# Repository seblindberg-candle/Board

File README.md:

# Candle Board

The EAGLE Cad board files for the Candle project can be found here.

## TODO

- [x] Add a pull-up on the flash memory chip select line.
- [x] Fix the MOSFET orientation.
- [x] Fix the flash memory footprint.
- [x] Remove the hole.
- [x] Remove the microphone
- [ ] Switch out the power supply.
- [ ] Move the status LEDs to the back.
- [ ] Move the button to a more reachable position
- [ ] Make the serial port easier to connect to
- [ ] Increase the board length to 25-30 cm
- [x] Bias the display driver current sense line with the DAC
- [ ] Add one or two light sensors (front and/or back)

The following hardware changes are based on features/limitations in the peripherals that where not discovered until after the first revision.

- [ ] Connect the flash memory to `SPIC`
- [ ] Connect the display driver to `USARTD0`
- [ ] Connect `DISP_LE` to an event output (`PC4`, `PC7`, `PD4` or `PD7`)
- [ ] Connect `DISP_OE` to a compare output (`PD2`, since it is unused)
- [ ] Connect the board serial port to `USARTC0`

## Revisions

Board revisions are kept as tags in git. The board is generally tagged when the files have been sent off for manufacturing. To export a specific revision, simply run

```
$ git archive --format zip -o /path/to/rev-a.zip 4d268f
```

where the hash of the tag can be found by running `git show rev-a` for the specific tag.

## Notes

### MOSFET Pull-ups

The pull-ups are required because of the internal protection diods in the main IC. They will not allow the voltage to exceed ~3.8 V. The resistors connected to the gates thus serve to:

1. protect the gate from inrush current,
2. pull the gate high on startup and
3. set the voltage at the gate to a value above the turn-on threshold.

## Scripts

Some ruby scripts are included for generating EAGLE commands that place some of the more repetitive components. There are tools in EAGLE for achieving the same thing and they are most likely better, but a) I did not know that at the time and b) the scripts allowed be to also remove the labels, which would otherwise have been quite a task in itself. 

To run the scripts you need to locate the Scripts folder in your terminal of choice and type `ruby place-diods.rb`. Then press `enter` and copy the output into the command input in EAGLE.

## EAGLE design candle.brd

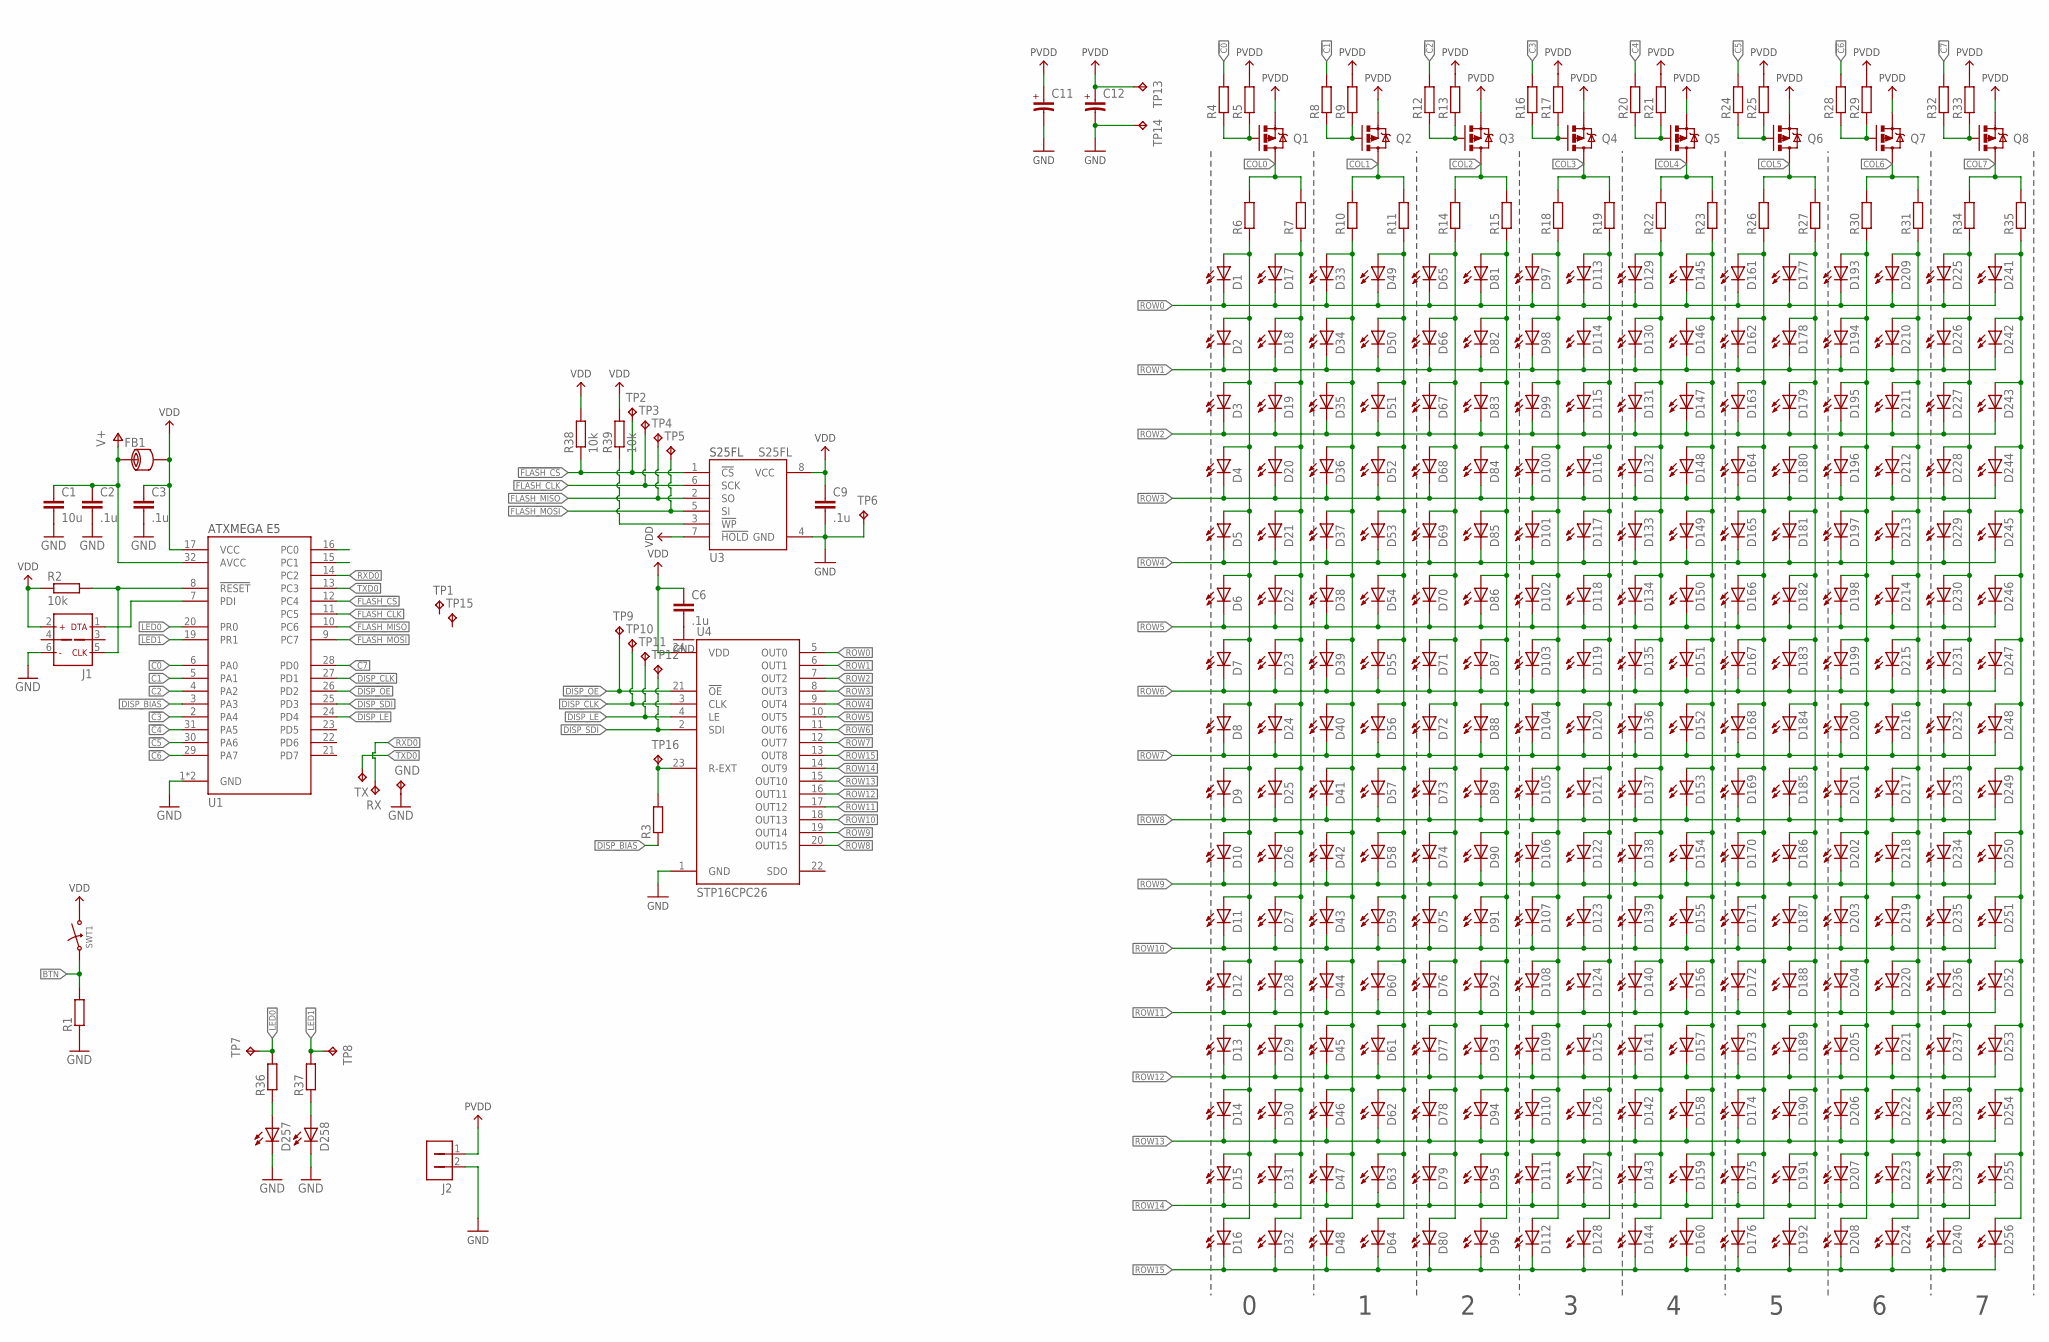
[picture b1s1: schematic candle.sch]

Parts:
C1: 10u; 0805
C2, C3, C6, C9: .1u; 0805
C11, C12: C_POL_1206; 1206_POL
D1, D2, D3, D4, D5, D6, D7, D8, D9, D10, D11, D12, D13, D14, D15, D16, D17, D18, D19, D20, D21, D22, D23, D24, D25, D26, D27, D28, D29, D30, D31, D32, D33, D34, D35, D36, D37, D38, D39, D40, D41, D42, D43, D44, D45, D46, D47, D48, D49, D50, D51, D52, D53, D54, D55, D56, D57, D58, D59, D60, D61, D62, D63, D64, D65, D66, D67, D68, D69, D70, D71, D72, D73, D74, D75, D76, D77, D78, D79, D80, D81, D82, D83, D84, D85, D86, D87, D88, D89, D90, D91, D92, D93, D94, D95, D96, D97, D98, D99, D100, D101, D102, D103, D104, D105, D106, D107, D108, D109, D110, D111, D112, D113, D114, D115, D116, D117, D118, D119, D120, D121, D122, D123, D124, D125, D126, D127, D128, D129, D130, D131, D132, D133, D134, D135, D136, D137, D138, D139, D140, D141, D142, D143, D144, D145, D146, D147, D148, D149, D150, D151, D152, D153, D154, D155, D156, D157, D158, D159, D160, D161, D162, D163, D164, D165, D166, D167, D168, D169, D170, D171, D172, D173, D174, D175, D176, D177, D178, D179, D180, D181, D182, D183, D184, D185, D186, D187, D188, D189, D190, D191, D192, D193, D194, D195, D196, D197, D198, D199, D200, D201, D202, D203, D204, D205, D206, D207, D208, D209, D210, D211, D212, D213, D214, D215, D216, D217, D218, D219, D220, D221, D222, D223, D224, D225, D226, D227, D228, D229, D230, D231, D232, D233, D234, D235, D236, D237, D238, D239, D240, D241, D242, D243, D244, D245, D246, D247, D248, D249, D250, D251, D252, D253, D254, D255, D256, D257, D258: LED_0805; 0805_LED
FB1: FB_0603; 0603
GND: TPB1,27; B1,27
J1: PDI_LOCK; 2X3_LOCK
J2: 1X2_MOLEX_53254
Q1, Q2, Q3, Q4, Q5, Q6, Q7, Q8: PMV160UP; SOT23
R1, R3, R4, R5, R6, R7, R8, R9, R10, R11, R12, R13, R14, R15, R16, R17, R18, R19, R20, R21, R22, R23, R24, R25, R26, R27, R28, R29, R30, R31, R32, R33, R34, R35, R36, R37: R_0603; 0603
R2: 10k; 0805
R38, R39: 10k; 0603
RX: TPB1,27; B1,27
SWT1: BUTTON_SMD_2P; BTN_SMD_2PIN
TP1, TP2, TP3, TP4, TP5, TP6, TP7, TP8, TP9, TP10, TP11, TP12, TP13, TP14, TP15, TP16: TPB1,27; B1,27
TX: TPB1,27; B1,27
U1: ATXMEGA_E5_TQFP; TQFP32
U3: S25FL; SO8
U4: STP16CPC26TSSOP24; TSSOP24

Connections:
!C0: R4.2, U1.6 (PA0)
!C0_: Q1.1 (G), R4.1, R5.1
!C1: R8.2, U1.5 (PA1)
!C2: R12.2, U1.4 (PA2)
!C3: R16.2, U1.2 (PA4)
!C3_: Q4.1 (G), R16.1, R17.1
!C4: R20.2, U1.31 (PA5)
!C5: R24.2, U1.30 (PA6)
!C5_: Q6.1 (G), R24.1, R25.1
!C6: R28.2, U1.29 (PA7)
!C6_: Q7.1 (G), R28.1, R29.1
!C7: R32.2, U1.28 (PD0)
!C7_: Q8.1 (G), R32.1, R33.1
!DISP_OE: TP9.TP, U1.26 (PD2), U4.21 (!OE)
!FLASH_CS: R38.1, TP2.TP, U1.12 (PC4), U3.1 (!CS)
!RESET: J1.5 (CLK), R2.2, U1.8 (!RESET)
BTN: R1.2, SWT1.1
COL0: Q1.3 (D), R6.2, R7.2
COL1: Q2.3 (D), R10.2, R11.2
COL2: Q3.3 (D), R14.2, R15.2
COL3: Q4.3 (D), R18.2, R19.2
COL4: Q5.3 (D), R22.2, R23.2
COL5: Q6.3 (D), R26.2, R27.2
COL6: Q7.3 (D), R30.2, R31.2
COL7: Q8.3 (D), R34.2, R35.2
DISP_BIAS: R3.1, U1.3 (PA3)
DISP_CLK: TP10.TP, U1.27 (PD1), U4.3 (CLK)
DISP_LE: TP11.TP, U1.24 (PD4), U4.4 (LE)
DISP_SDI: TP12.TP, U1.25 (PD3), U4.2 (SDI)
FLASH_CLK: TP3.TP, U1.11 (PC5), U3.6 (SCK)
FLASH_MISO: TP4.TP, U1.10 (PC6), U3.2 (SO)
FLASH_MOSI: TP5.TP, U1.9 (PC7), U3.5 (SI)
GND: C1.2, C2.2, C3.2, C6.2, C9.2, C11.2, C12.2, D257.C, D258.C, GND.TP, J1.6 (GND), J2.2, R1.1, TP6.TP, TP14.TP, U1.1 (GND), U1.18 (GND), U3.4 (GND), U4.1 (GND)
LED0: R36.2, TP7.TP, U1.20 (PR0)
LED1: R37.2, TP8.TP, U1.19 (PR1)
unnamed: D257.A, R36.1
unnamed: D1.A, D2.A, D3.A, D4.A, D5.A, D6.A, D7.A, D8.A, D9.A, D10.A, D11.A, D12.A, D13.A, D14.A, D15.A, D16.A, R6.1
unnamed: D17.A, D18.A, D19.A, D20.A, D21.A, D22.A, D23.A, D24.A, D25.A, D26.A, D27.A, D28.A, D29.A, D30.A, D31.A, D32.A, R7.1
unnamed: D258.A, R37.1
unnamed: R39.1, U3.3 (!WP)
unnamed: Q2.1 (G), R8.1, R9.1
unnamed: D65.A, D66.A, D67.A, D68.A, D69.A, D70.A, D71.A, D72.A, D73.A, D74.A, D75.A, D76.A, D77.A, D78.A, D79.A, D80.A, R14.1
unnamed: D81.A, D82.A, D83.A, D84.A, D85.A, D86.A, D87.A, D88.A, D89.A, D90.A, D91.A, D92.A, D93.A, D94.A, D95.A, D96.A, R15.1
unnamed: R3.2, TP16.TP, U4.23 (R-EXT)
unnamed: D129.A, D130.A, D131.A, D132.A, D133.A, D134.A, D135.A, D136.A, D137.A, D138.A, D139.A, D140.A, D141.A, D142.A, D143.A, D144.A, R22.1
unnamed: D145.A, D146.A, D147.A, D148.A, D149.A, D150.A, D151.A, D152.A, D153.A, D154.A, D155.A, D156.A, D157.A, D158.A, D159.A, D160.A, R23.1
unnamed: Q3.1 (G), R12.1, R13.1
unnamed: Q5.1 (G), R20.1, R21.1
unnamed: D97.A, D98.A, D99.A, D100.A, D101.A, D102.A, D103.A, D104.A, D105.A, D106.A, D107.A, D108.A, D109.A, D110.A, D111.A, D112.A, R18.1
unnamed: D113.A, D114.A, D115.A, D116.A, D117.A, D118.A, D119.A, D120.A, D121.A, D122.A, D123.A, D124.A, D125.A, D126.A, D127.A, D128.A, R19.1
unnamed: D161.A, D162.A, D163.A, D164.A, D165.A, D166.A, D167.A, D168.A, D169.A, D170.A, D171.A, D172.A, D173.A, D174.A, D175.A, D176.A, R26.1
unnamed: D177.A, D178.A, D179.A, D180.A, D181.A, D182.A, D183.A, D184.A, D185.A, D186.A, D187.A, D188.A, D189.A, D190.A, D191.A, D192.A, R27.1
unnamed: D193.A, D194.A, D195.A, D196.A, D197.A, D198.A, D199.A, D200.A, D201.A, D202.A, D203.A, D204.A, D205.A, D206.A, D207.A, D208.A, R30.1
unnamed: D209.A, D210.A, D211.A, D212.A, D213.A, D214.A, D215.A, D216.A, D217.A, D218.A, D219.A, D220.A, D221.A, D222.A, D223.A, D224.A, R31.1
unnamed: D225.A, D226.A, D227.A, D228.A, D229.A, D230.A, D231.A, D232.A, D233.A, D234.A, D235.A, D236.A, D237.A, D238.A, D239.A, D240.A, R34.1
unnamed: D241.A, D242.A, D243.A, D244.A, D245.A, D246.A, D247.A, D248.A, D249.A, D250.A, D251.A, D252.A, D253.A, D254.A, D255.A, D256.A, R35.1
unnamed: D33.A, D34.A, D35.A, D36.A, D37.A, D38.A, D39.A, D40.A, D41.A, D42.A, D43.A, D44.A, D45.A, D46.A, D47.A, D48.A, R10.1
unnamed: D49.A, D50.A, D51.A, D52.A, D53.A, D54.A, D55.A, D56.A, D57.A, D58.A, D59.A, D60.A, D61.A, D62.A, D63.A, D64.A, R11.1
PDI: J1.1 (DATA), U1.7 (PDI)
PVDD: C11.1, C12.1, J2.1, Q1.2 (S), Q2.2 (S), Q3.2 (S), Q4.2 (S), Q5.2 (S), Q6.2 (S), Q7.2 (S), Q8.2 (S), R5.2, R9.2, R13.2, R17.2, R21.2, R25.2, R29.2, R33.2, TP13.TP
ROW0: D1.C, D17.C, D33.C, D49.C, D65.C, D81.C, D97.C, D113.C, D129.C, D145.C, D161.C, D177.C, D193.C, D209.C, D225.C, D241.C, U4.5 (OUT0)
ROW1: D2.C, D18.C, D34.C, D50.C, D66.C, D82.C, D98.C, D114.C, D130.C, D146.C, D162.C, D178.C, D194.C, D210.C, D226.C, D242.C, U4.6 (OUT1)
ROW2: D3.C, D19.C, D35.C, D51.C, D67.C, D83.C, D99.C, D115.C, D131.C, D147.C, D163.C, D179.C, D195.C, D211.C, D227.C, D243.C, U4.7 (OUT2)
ROW3: D4.C, D20.C, D36.C, D52.C, D68.C, D84.C, D100.C, D116.C, D132.C, D148.C, D164.C, D180.C, D196.C, D212.C, D228.C, D244.C, U4.8 (OUT3)
ROW4: D5.C, D21.C, D37.C, D53.C, D69.C, D85.C, D101.C, D117.C, D133.C, D149.C, D165.C, D181.C, D197.C, D213.C, D229.C, D245.C, U4.9 (OUT4)
ROW5: D6.C, D22.C, D38.C, D54.C, D70.C, D86.C, D102.C, D118.C, D134.C, D150.C, D166.C, D182.C, D198.C, D214.C, D230.C, D246.C, U4.10 (OUT5)
ROW6: D7.C, D23.C, D39.C, D55.C, D71.C, D87.C, D103.C, D119.C, D135.C, D151.C, D167.C, D183.C, D199.C, D215.C, D231.C, D247.C, U4.11 (OUT6)
ROW7: D8.C, D24.C, D40.C, D56.C, D72.C, D88.C, D104.C, D120.C, D136.C, D152.C, D168.C, D184.C, D200.C, D216.C, D232.C, D248.C, U4.12 (OUT7)
ROW8: D9.C, D25.C, D41.C, D57.C, D73.C, D89.C, D105.C, D121.C, D137.C, D153.C, D169.C, D185.C, D201.C, D217.C, D233.C, D249.C, U4.20 (OUT15)
ROW9: D10.C, D26.C, D42.C, D58.C, D74.C, D90.C, D106.C, D122.C, D138.C, D154.C, D170.C, D186.C, D202.C, D218.C, D234.C, D250.C, U4.19 (OUT14)
ROW10: D11.C, D27.C, D43.C, D59.C, D75.C, D91.C, D107.C, D123.C, D139.C, D155.C, D171.C, D187.C, D203.C, D219.C, D235.C, D251.C, U4.18 (OUT13)
ROW11: D12.C, D28.C, D44.C, D60.C, D76.C, D92.C, D108.C, D124.C, D140.C, D156.C, D172.C, D188.C, D204.C, D220.C, D236.C, D252.C, U4.17 (OUT12)
ROW12: D13.C, D29.C, D45.C, D61.C, D77.C, D93.C, D109.C, D125.C, D141.C, D157.C, D173.C, D189.C, D205.C, D221.C, D237.C, D253.C, U4.16 (OUT11)
ROW13: D14.C, D30.C, D46.C, D62.C, D78.C, D94.C, D110.C, D126.C, D142.C, D158.C, D174.C, D190.C, D206.C, D222.C, D238.C, D254.C, U4.15 (OUT10)
ROW14: D15.C, D31.C, D47.C, D63.C, D79.C, D95.C, D111.C, D127.C, D143.C, D159.C, D175.C, D191.C, D207.C, D223.C, D239.C, D255.C, U4.14 (OUT9)
ROW15: D16.C, D32.C, D48.C, D64.C, D80.C, D96.C, D112.C, D128.C, D144.C, D160.C, D176.C, D192.C, D208.C, D224.C, D240.C, D256.C, U4.13 (OUT8)
RXD0: RX.TP, U1.14 (PC2)
TXD0: TX.TP, U1.13 (PC3)
V+: C1.1, C2.1, FB1.1, U1.32 (AVCC)
VDD: C3.1, C6.1, C9.1, FB1.2, J1.2 (VCC), R2.1, R38.2, R39.2, SWT1.2, U1.17 (VCC), U3.7 (!HOLD), U3.8 (VCC), U4.24 (VDD)

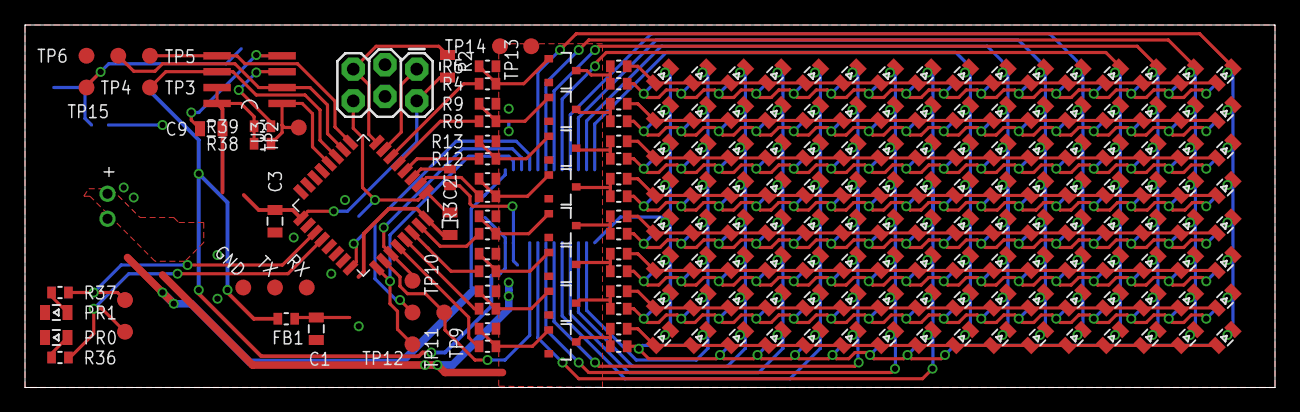
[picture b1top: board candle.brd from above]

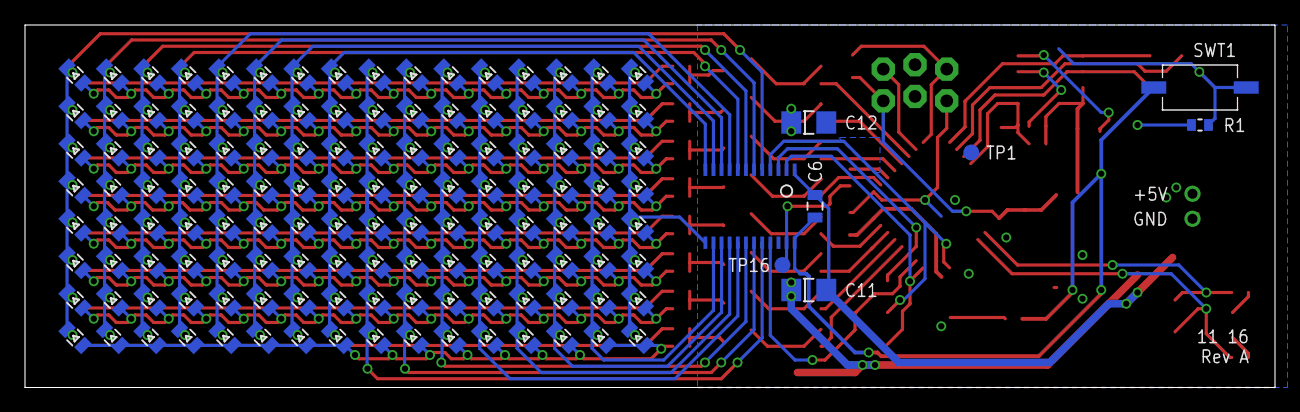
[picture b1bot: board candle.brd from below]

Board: 2 copper layers, 100.0 x 29.0 mm, 338 parts (137 on the bottom side), 80 nets.

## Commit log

2017-11-12 Added a readme
2017-11-12 Removed microphone and some connectors
2017-12-19 Fixed the transistor pinout error and updated eagle
2017-12-21 Added some TODOs
2017-12-21 Rewired the flash chip and rotated the mosfets
2017-12-21 Ignore lock files
2017-12-21 Added a note on the pull-ups
2017-12-21 Cleaned up the flash and removed unused pins
2017-12-21 Added some todos and verified the flash foodprint
2018-01-09 Now ignores the Eagle settings file
2018-01-09 Removed Eagle settings file
2018-01-09 Added an image of the first prototype
2018-01-09 Added a note on the included ruby scripts
